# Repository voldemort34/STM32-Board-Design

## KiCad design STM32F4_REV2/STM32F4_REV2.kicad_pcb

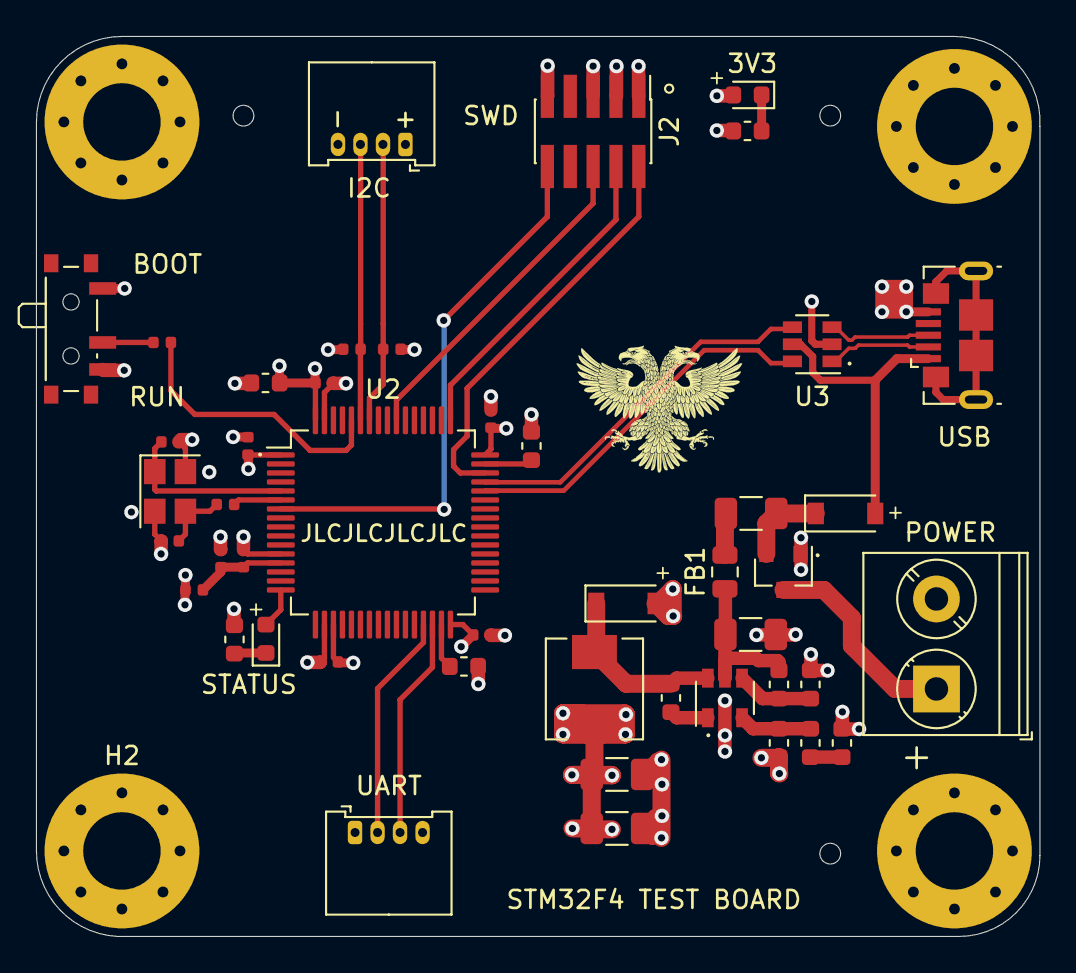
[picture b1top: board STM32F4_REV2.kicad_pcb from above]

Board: 4 copper layers, 55.8 x 50.0 mm, 50 parts (0 on the bottom side), 31 nets.

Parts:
C1, C2, C3: 10u; C_1206_3216Metric
C4: 10n; C_0603_1608Metric
C5: 4u7; C_0603_1608Metric
C6, C7, C8, C9, C10: 100n; C_0402_1005Metric
C11: 1u; C_0402_1005Metric
C12: 10n; C_0402_1005Metric
C13, C14: 2u2; C_0603_1608Metric
C15, C16: 12p; C_0402_1005Metric
D1, D2: B5819W; D_SOD-123
D3: RED; LED_0603_1608Metric
D4: BLUE; LED_0603_1608Metric
F1: 250mA; Fuse_1206_3216Metric
FB1: 600 @ 600 MHz; L_0805_2012Metric
H1, H2, H3, H4: MountingHole_Pad; MountingHole_4.3mm_M4_Pad_Via
J1: Screw_Terminal_01x02; TerminalBlock_Phoenix_PT-1,5-2-5.0-H_1x02_P5.00mm_Horizontal
J2: SWD; PinHeader_2x05_P1.27mm_Vertical_SMD
J3, J4: Conn_01x04; Molex_PicoBlade_53048-0410_1x04_P1.25mm_Horizontal
J5: USB_B_Micro; USB_Micro-B_GCT_USB3076-30-A
L1: 10u; L_Sunlord_MWSA0518_5.4x5.2mm
L2: 39n; L_0402_1005Metric
Q1: AO3401A; SOT-23
R1: 100k; R_0603_1608Metric
R2: 68k; R_0603_1608Metric
R3: 47k; R_0603_1608Metric
R4: 15k; R_0603_1608Metric
R5: 270; R_0603_1608Metric
R6: 1k; R_0603_1608Metric
R7: 10k; R_0402_1005Metric
R8: 47; R_0402_1005Metric
R9: 1k5; R_0603_1608Metric
R10, R11: 2k2; R_0402_1005Metric
SW1: SW_SPDT; SW_SPDT_PCM12
U1: MP2359DJ-LF-Z; SOT-23-6
U2: STM32F405RGT6; LQFP-64_10x10mm_P0.5mm
U3: USBLC6-2SC6; SOT-23-6
Y1: 16MHz; Crystal_SMD_3225-4Pin_3.2x2.5mm

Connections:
+3.3VA: C11.1, C12.1, L2.2, U2.13
+3V3: C2.1, C3.1, C5.1, C6.1, C7.1, C8.1, C9.1, C10.1, D3.2, J2.1, J3.1, J4.1, L1.2, L2.1, R3.1, R10.1, R11.1, SW1.1, U2.1, U2.19, U2.32, U2.48, U2.64
+5V: D1.2, J5.1
+12V: J1.1, Q1.3
BOOT0: R7.2, U2.60
BUCK_BST: C4.2, U1.1
BUCK_EN: R1.2, R2.1, U1.4
BUCK_FB: R3.2, R4.1, U1.3
BUCK_IN: C1.1, FB1.1, R1.1, U1.5
BUCK_SW: C4.1, D2.1, L1.1, U1.6
GND: C1.2, C2.2, C3.2, C5.2, C6.2, C7.2, C8.2, C9.2, C10.2, C11.2, C12.2, C13.2, C14.2, C15.2, C16.2, D2.2, H1.1, H2.1, H3.1, H4.1, J1.2, J2.3, J2.5, J2.9, J3.4, J4.4, J5.5, Q1.1, R2.2, R5.2, R6.2, R9.2, SW1.3, U1.2, U2.12, U2.18, U2.63, Y1.2, Y1.4
HSE_IN: C15.1, U2.5, Y1.1
HSE_OUT: R8.1, U2.6
I2C1_SCL: J3.2, R10.2, U2.58
I2C1_SDA: J3.3, R11.2, U2.59
LED_STATUS: D4.2, U2.16
NRST: J2.10, U2.7
unnamed: C13.1, U2.31
unnamed: C14.1, U2.47
unnamed: C16.1, R8.2, Y1.3
unnamed: D1.1, F1.2, Q1.2
unnamed: D3.1, R6.1
unnamed: D4.1, R9.1
unnamed: F1.1, FB1.2
unnamed: R4.2, R5.1
unnamed: R7.1, SW1.2
SWCLK: J2.4, U2.49
SWDIO: J2.2, U2.46
SWO: J2.6, U2.55
USART3_RX: J4.3, U2.30
USART3_TX: J4.2, U2.29

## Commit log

2023-08-22 altium
2023-08-28 STM32F4_Kicad
